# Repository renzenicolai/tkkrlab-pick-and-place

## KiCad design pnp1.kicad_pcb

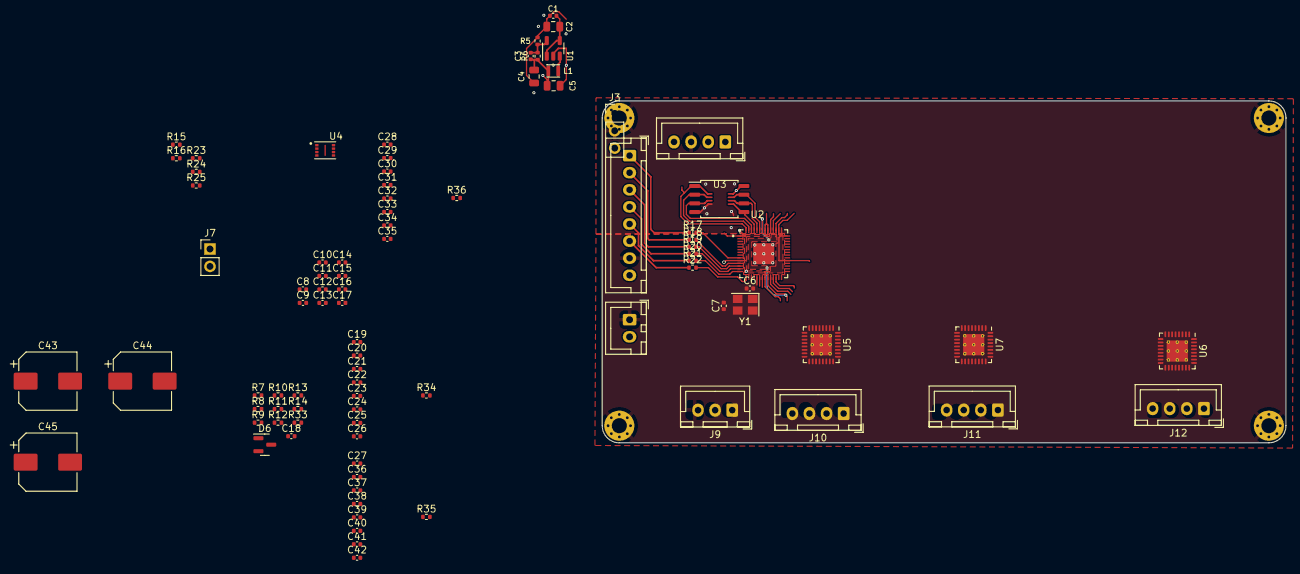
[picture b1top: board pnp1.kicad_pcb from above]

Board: 4 copper layers, 100.0 x 50.0 mm, 93 parts (0 on the bottom side), 76 nets.

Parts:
C1, C8, C10, C11, C13, C14, C15, C16, C17, C19, C23, C24, C27, C28, C32, C33, C39, C40: 100n; C_0402_1005Metric
C2, C4, C5: 22u; C_0805_2012Metric
C3, C6, C7: 22p; C_0402_1005Metric
C9, C12, C18, C22, C25, C26, C31, C34, C35, C38, C41, C42: 1u; C_0402_1005Metric
C20, C29, C36: 2.2u; C_0402_1005Metric
C21, C30, C37: 22n; C_0402_1005Metric
C43, C44, C45: 100u; CP_Elec_8x10
D6: BAT54A; SOT-23
H1, H2, H3, H4: MountingHole_Pad; MountingHole_2.2mm_M2_Pad_Via
J1: USB; JST_XH_B4B-XH-A_1x04_P2.50mm_Vertical
J2: VM; JST_XH_B2B-XH-A_1x02_P2.50mm_Vertical
J3: SWD; PinHeader_1x03_P2.54mm_Vertical
J6: EXT_SPI; JST_XH_B8B-XH-A_1x08_P2.50mm_Vertical
J7: BOOT; PinHeader_1x02_P2.54mm_Vertical
J9: Sensor; JST_XH_B3B-XH-A_1x03_P2.50mm_Vertical
J10, J11, J12: Motor; JST_XH_B4B-XH-A_1x04_P2.50mm_Vertical
L1: 2.2u; Inductor_MSC20FC
R5, R7, R8, R9, R10, R11, R12, R13, R14: 10k; R_0402_1005Metric
R6: 45.3k; R_0402_1005Metric
R15, R16, R25: 1k; R_0402_1005Metric
R17, R18, R19, R20, R21, R22, R23, R24: 27; R_0402_1005Metric
R33: 4.7k; R_0402_1005Metric
R34, R35, R36: 48k; R_0402_1005Metric
U1: SY8079AAC; SOT-23-5
U2: RP2040; QFN40P700X700X90-57N
U3: W25Q16JVUXIQ; SOIC-8_5.23x5.23mm_P1.27mm
U4: W25Q16JVUXIQ; PSON50P300X200X60-9N
U5, U6, U7: TQFN-32-1EP_5x5mm_P0.5mm_EP3.1x3.1mm_ThermalVias
Y1: 12MHz; Crystal_SMD_3225-4Pin_3.2x2.5mm

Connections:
+1V1: C12.1, C14.1, C16.1, U2.23 (DVDD), U2.45 (VREG_VOUT), U2.50 (DVDD)
+3V3: C3.1, C4.1, C5.1, C8.1, C9.1, C10.1, C11.1, C13.1, C15.1, C17.1, C19.1, C27.1, C28.1, L1.1, R6.1, R7.1, R8.1, R9.1, R10.1, R11.1, R12.1, R13.1, R14.1, R16.2, R33.1, U2.1 (IOVDD), U2.10 (IOVDD), U2.22 (IOVDD), U2.33 (IOVDD), U2.42 (IOVDD), U2.43 (ADC_AVDD), U2.44 (VREG_VIN), U2.48 (USB_VDD), U2.49 (IOVDD), U3.8 (VDD), U4.8 (VDD), U5.5 (VCCIO), U6.5 (VCCIO), U7.5 (VCCIO)
+5V: C1.1, C2.1, J1.4, J6.8, U1.1 (EN), U1.4 (VIN)
+24V: C18.2, C22.2, C23.1, C24.1, C25.2, C26.2, C31.2, C32.1, C33.1, C34.2, C35.2, C38.2, C39.1, C40.1, C41.2, C42.2, C43.1, C44.1, C45.1, J2.2, J9.3, U5.17 (VS1), U5.20 (VS2), U5.21 (VS3), U5.24 (VS4), U6.17 (VS1), U6.20 (VS2), U6.21 (VS3), U6.24 (VS4), U7.17 (VS1), U7.20 (VS2), U7.21 (VS3), U7.24 (VS4)
/FB33: C3.2, R5.1, R6.2, U1.5 (FB)
/Motor1/CS: R7.2, U2.38 (GPIO26/ADC0), U5.26 (CSN/AD2), U6.27 (SCK/AD1), U7.27 (SCK/AD1)
/Motor1/INT: R10.2, U2.32 (GPIO21), U5.11 (DIAG0)
/Motor1/MISO: U2.31 (GPIO20), U5.29 (SDO/NAO), U6.29 (SDO/NAO), U7.29 (SDO/NAO)
/Motor1/MOSI: U2.30 (GPIO19), U5.28 (SDI/AD0), U6.28 (SDI/AD0), U7.28 (SDI/AD0)
/Motor1/REFL: D6.3, R33.2, U5.31 (REFL)
/Motor1/SCK: U2.29 (GPIO18), U5.27 (SCK/AD1)
/Motor1/~DRV_EN: R13.2, U2.28 (GPIO17), U5.9 (~DRV_EN), U6.9 (~DRV_EN), U7.9 (~DRV_EN)
/Motor1/~SLEEP: R14.2, U2.27 (GPIO16), U5.25 (~SLEEP), U6.25 (~SLEEP), U7.25 (~SLEEP)
/Motor2/CS: R8.2, U2.37 (GPIO25), U6.26 (CSN/AD2)
/Motor2/INT: R11.2, U2.34 (GPIO22), U6.11 (DIAG0)
/Motor3/CS: R9.2, U2.36 (GPIO24), U7.26 (CSN/AD2)
/Motor3/INT: R12.2, U2.35 (GPIO23), U7.11 (DIAG0)
/RP2040/RP_BTN: J7.2, R25.2
/RP2040/RP_QSPI_CSN: R25.1, U2.56 (QSPI_CSN), U3.1 (~CS), U4.1 (~CS)
/RP2040/RP_QSPI_SCLK: U2.52 (QSPI_SCLK), U3.6 (SCK), U4.6 (SCK)
/RP2040/RP_QSPI_SD0: U2.53 (QSPI_SD0), U3.5 (MOSI/IO0), U4.5 (MOSI/IO0)
/RP2040/RP_QSPI_SD1: U2.55 (QSPI_SD1), U3.2 (MISO/IO1), U4.2 (MISO/IO1)
/RP2040/RP_QSPI_SD2: U2.54 (QSPI_SD2), U3.3 (IO2), U4.3 (IO2)
/RP2040/RP_QSPI_SD3: U2.51 (QSPI_SD3), U3.7 (IO3), U4.7 (IO3)
/RP2040/RP_XIN: C6.1, U2.20 (XIN), Y1.1
/RP2040/RP_XOUT: R15.2, U2.21 (XOUT)
/RP2040/SPI1_CS0: J6.3, R19.1
/RP2040/SPI1_CS1: J6.2, R18.1
/RP2040/SPI1_CS2: J6.1, R17.1
/RP2040/SPI1_MISO: J6.6, R22.1
/RP2040/SPI1_MOSI: J6.5, R21.1
/RP2040/SPI1_SCK: J6.4, R20.1
/RP2040/USB_DM: J1.2, R23.1
/RP2040/USB_DP: J1.1, R24.2
/SW33: L1.2, U1.3 (SW)
GND: C1.2, C2.2, C4.2, C5.2, C6.2, C7.2, C8.2, C9.2, C10.2, C11.2, C12.2, C13.2, C14.2, C15.2, C16.2, C17.2, C18.1, C19.2, C20.2, C23.2, C24.2, C25.1, C26.1, C27.2, C28.2, C29.2, C32.2, C33.2, C34.1, C35.1, C36.2, C39.2, C40.2, C41.1, C42.1, C43.2, C44.2, C45.2, H1.1, H2.1, H3.1, H4.1, J1.3, J2.1, J3.2, J6.7, J7.1, J9.1, R5.2, R34.2, R35.2, R36.2, U1.2 (GND), U2.19 (TESTEN), U2.57 (GND), U3.4 (VSS), U4.4 (VSS), U5.4 (AGND), U5.6 (ENCN), U5.7 (ENCB), U5.8 (ENCA), U5.10 (UART_EN), U5.30 (CLK), U5.32 (REFR), U5.33 (PAD), U6.4 (AGND), U6.6 (ENCN), U6.7 (ENCB), U6.8 (ENCA), U6.10 (UART_EN), U6.30 (CLK), U6.31 (REFL), U6.32 (REFR), U6.33 (PAD), U7.4 (AGND), U7.6 (ENCN), U7.7 (ENCB), U7.8 (ENCA), U7.10 (UART_EN), U7.30 (CLK), U7.31 (REFL), U7.32 (REFR), U7.33 (PAD), Y1.2, Y1.4
unnamed: C7.1, R15.1, Y1.3
unnamed: J3.1, U2.25 (SWD)
unnamed: J3.3, U2.24 (SWCLK)
unnamed: D6.2, J9.2
unnamed: J10.1, U5.23 (OUT1A)
unnamed: J10.2, U5.22 (OUT2A)
unnamed: J10.3, U5.19 (OUT2B)
unnamed: J10.4, U5.18 (OUT1B)
unnamed: J11.1, U7.23 (OUT1A)
unnamed: J11.2, U7.22 (OUT2A)
unnamed: J11.3, U7.19 (OUT2B)
unnamed: J11.4, U7.18 (OUT1B)
unnamed: J12.1, U6.23 (OUT1A)
unnamed: J12.2, U6.22 (OUT2A)
unnamed: J12.3, U6.19 (OUT2B)
unnamed: J12.4, U6.18 (OUT1B)
unnamed: R17.2, U2.9 (GPIO7)
unnamed: R18.2, U2.11 (GPIO8)
unnamed: R19.2, U2.12 (GPIO9)
unnamed: R20.2, U2.13 (GPIO10)
unnamed: R21.2, U2.14 (GPIO11)
unnamed: R22.2, U2.15 (GPIO12)
unnamed: R16.1, U2.26 (RUN)
unnamed: R23.2, U2.46 (USB_DM)
unnamed: R24.1, U2.47 (USB_DP)
unnamed: C21.1, U5.14 (CPI)
unnamed: C21.2, U5.15 (CPO)
unnamed: R34.1, U5.1 (IREF)
unnamed: C22.1, U5.16 (VCP)
unnamed: C20.1, U5.3 (VDD18)
unnamed: C30.1, U6.14 (CPI)
unnamed: C30.2, U6.15 (CPO)
unnamed: R36.1, U6.1 (IREF)
unnamed: C31.1, U6.16 (VCP)
unnamed: C29.1, U6.3 (VDD18)
unnamed: C37.1, U7.14 (CPI)
unnamed: C37.2, U7.15 (CPO)
unnamed: R35.1, U7.1 (IREF)
unnamed: C38.1, U7.16 (VCP)
unnamed: C36.1, U7.3 (VDD18)
